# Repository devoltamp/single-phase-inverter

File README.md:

[https://github.com/sunnyiisc/Single-Phase-Inverter-12VDC-to-240VAC-50Hz](https://github.com/sunnyiisc/Single-Phase-Inverter-12VDC-to-240VAC-50Hz) 
-- a huge thanks to this dude!  

---
<!-- - <a href="https://github.com/user-attachments/assets/0ff65525-b211-4417-b515-1229c8c8692c">detailed version</a> -->
> [!NOTE]
> click the image to view it clearly

https://github.com/user-attachments/assets/3dfe6765-0608-4ea1-a7e6-09f013bc383d

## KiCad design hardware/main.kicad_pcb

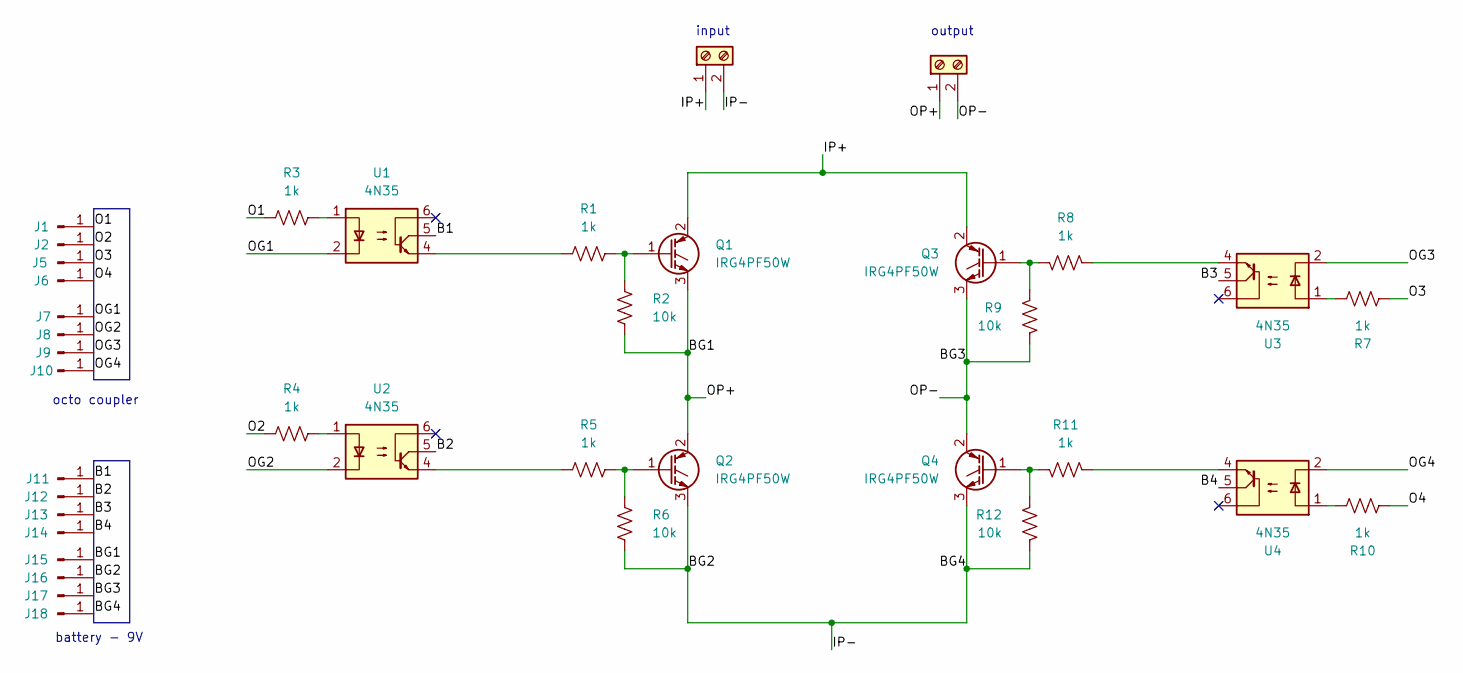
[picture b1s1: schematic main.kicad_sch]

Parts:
J1, J2, J5, J6, J7, J8, J9, J10, J11, J12, J13, J14, J15, J16, J17, J18: Conn_01x01_Pin; PinHeader_1x01_P2.54mm_Vertical
J3, J4: Screw_Terminal_01x02; TerminalBlock_CUI_TB007-508-02_1x02_P5.08mm_Horizontal
Q1, Q2, Q3, Q4: IRG4PF50W; TO-247-3_Vertical
R1, R3, R4, R5, R7, R8, R10, R11: 1k; R_Axial_DIN0204_L3.6mm_D1.6mm_P7.62mm_Horizontal
R2, R6, R9, R12: 10k; R_Axial_DIN0204_L3.6mm_D1.6mm_P7.62mm_Horizontal
U1, U2, U3, U4: 4N35; DIP-6_W7.62mm

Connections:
/B1: J11.1 (Pin_1_1), U1.5
/B2: J12.1 (Pin_1_1), U2.5
/B3: J13.1 (Pin_1_1), U3.5
/B4: J14.1 (Pin_1_1), U4.5
/BG1: J4.1, J15.1 (Pin_1_1), Q1.3 (E), Q2.2 (C), R2.2
/BG2: J3.2, J16.1 (Pin_1_1), J18.1 (Pin_1_1), Q2.3 (E), Q4.3 (E), R6.2, R12.2
/BG3: J4.2, J17.1 (Pin_1_1), Q3.3 (E), Q4.2 (C), R9.2
/IP+: J3.1, Q1.2 (C), Q3.2 (C)
/O1: J1.1 (Pin_1_1), R3.2
/O2: J2.1 (Pin_1_1), R4.2
/O3: J5.1 (Pin_1_1), R7.2
/O4: J6.1 (Pin_1_1), R10.2
/OG1: J7.1 (Pin_1_1), U1.2
/OG2: J8.1 (Pin_1_1), U2.2
/OG3: J9.1 (Pin_1_1), U3.2
/OG4: J10.1 (Pin_1_1), U4.2
unnamed: Q1.1 (G), R1.1, R2.1
unnamed: Q2.1 (G), R5.1, R6.1
unnamed: Q3.1 (G), R8.1, R9.1
unnamed: Q4.1 (G), R11.1, R12.1
unnamed: R1.2, U1.4
unnamed: R3.1, U1.1
unnamed: R4.1, U2.1
unnamed: R5.2, U2.4
unnamed: R7.1, U3.1
unnamed: R8.2, U3.4
unnamed: R10.1, U4.1
unnamed: R11.2, U4.4

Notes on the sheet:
octo coupler
battery - 9V
input
output

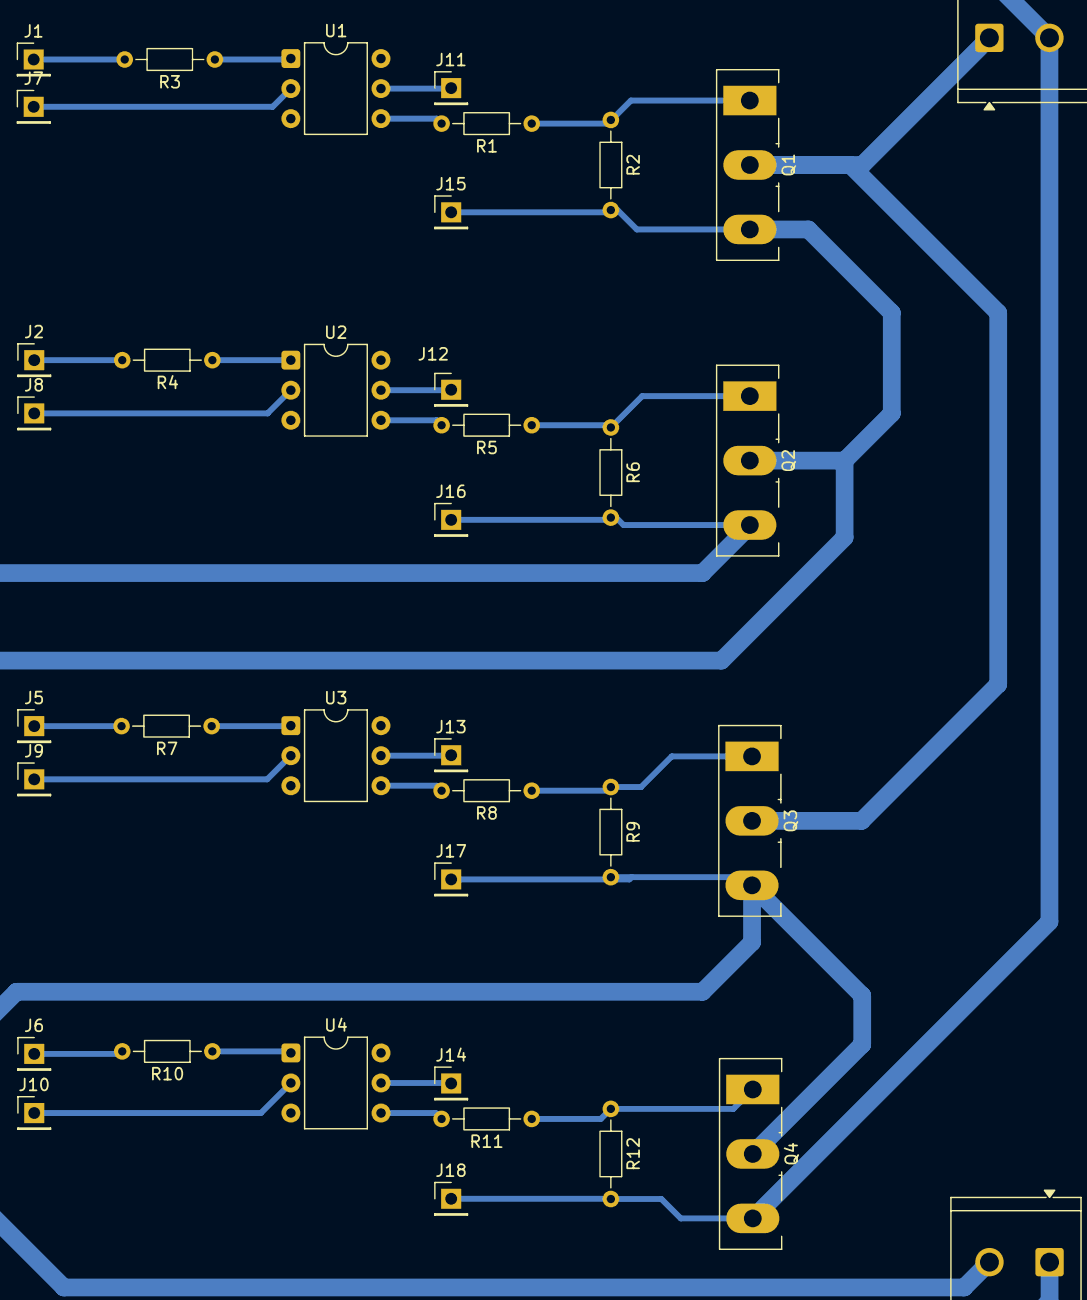
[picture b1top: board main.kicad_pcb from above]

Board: 2 copper layers, 38 parts (0 on the bottom side), 28 nets.
